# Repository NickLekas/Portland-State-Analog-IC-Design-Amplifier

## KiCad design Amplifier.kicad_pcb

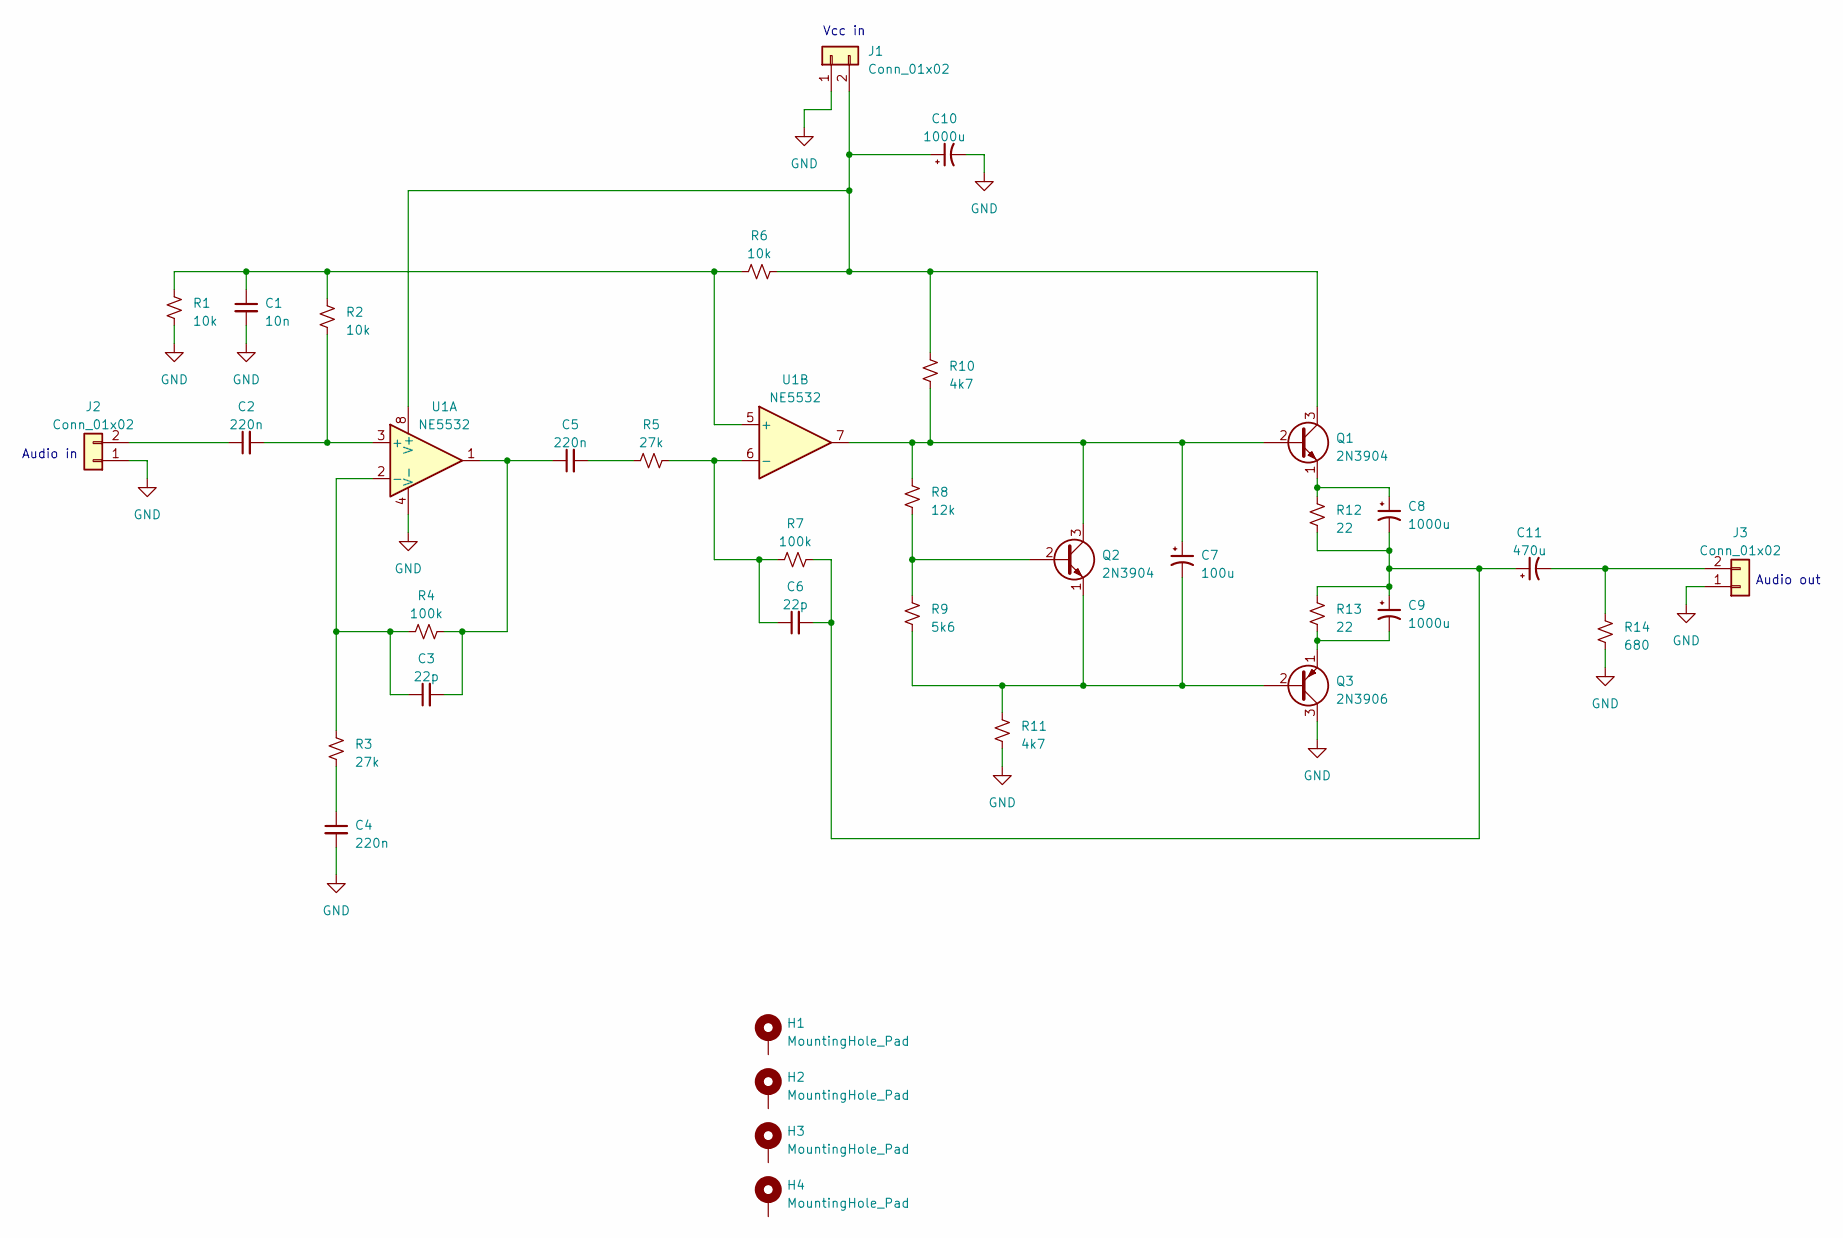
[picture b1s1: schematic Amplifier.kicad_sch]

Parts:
C1: 10n; C_Rect_L7.0mm_W2.5mm_P5.00mm
C2, C4, C5: 220n; C_Rect_L7.0mm_W2.5mm_P5.00mm
C3, C6: 22p; C_Rect_L7.0mm_W2.5mm_P5.00mm
C7: 100u; CP_Radial_D8.0mm_P3.50mm
C8, C9, C10: 1000u; CP_Radial_D10.0mm_P5.00mm
C11: 470u; CP_Radial_D10.0mm_P5.00mm
H1, H2, H3, H4: MountingHole_Pad; MountingHole_3.2mm_M3_Pad_TopBottom
J1, J2, J3: Conn_01x02; TerminalBlock_Altech_AK300-2_P5.00mm
Q1, Q2: 2N3904; TO-92_Inline_Wide
Q3: 2N3906; TO-92_Inline_Wide
R1, R2, R6: 10k; R_Axial_DIN0207_L6.3mm_D2.5mm_P10.16mm_Horizontal
R3, R5: 27k; R_Axial_DIN0207_L6.3mm_D2.5mm_P10.16mm_Horizontal
R4, R7: 100k; R_Axial_DIN0207_L6.3mm_D2.5mm_P10.16mm_Horizontal
R8: 12k; R_Axial_DIN0207_L6.3mm_D2.5mm_P10.16mm_Horizontal
R9: 5k6; R_Axial_DIN0207_L6.3mm_D2.5mm_P10.16mm_Horizontal
R10, R11: 4k7; R_Axial_DIN0207_L6.3mm_D2.5mm_P10.16mm_Horizontal
R12, R13: 22; R_Axial_DIN0207_L6.3mm_D2.5mm_P10.16mm_Horizontal
R14: 680; R_Axial_DIN0207_L6.3mm_D2.5mm_P10.16mm_Horizontal
U1: NE5532; DIP-8_W10.16mm

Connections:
GND: C1.2, C4.2, C10.2, J1.1, J2.1, J3.1, Q3.3 (C), R1.2, R11.2, R14.2, U1.4 (V-)
unnamed: C3.2, C5.1, R4.2, U1.1
unnamed: C4.1, R3.2
unnamed: C5.2, R5.1
unnamed: C6.2, C8.2, C9.1, C11.1, R7.2, R12.2, R13.1
unnamed: C10.1, J1.2, Q1.3 (C), R6.2, R10.1, U1.8 (V+)
unnamed: C2.1, J2.2
unnamed: C11.2, J3.2, R14.1
unnamed: C7.1, Q1.2 (B), Q2.3 (C), R8.1, R10.2, U1.7
unnamed: C8.1, Q1.1 (E), R12.1
unnamed: Q2.2 (B), R8.2, R9.1
unnamed: C7.2, Q2.1 (E), Q3.2 (B), R9.2, R11.1
unnamed: C9.2, Q3.1 (E), R13.2
unnamed: C2.2, R2.2, U1.3 (+)
unnamed: C3.1, R3.1, R4.1, U1.2 (-)
unnamed: C1.1, R1.1, R2.1, R6.1, U1.5 (+)
unnamed: C6.1, R5.2, R7.1, U1.6 (-)

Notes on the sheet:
Vcc in
Audio in
Audio out

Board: 2 copper layers, 36 parts (0 on the bottom side), 17 nets, no tracks yet.

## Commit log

2023-04-13 added legacy schematic
2023-04-14 added initial footprints for components
2023-04-14 assigned real footprints based on what we have in the EPL
2023-04-14 mid layout check-in
2023-04-14 layout work and added M3 mounting holes
